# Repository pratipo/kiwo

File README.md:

# kiwo
post digital knitting, hybrid fabrication, digital crafts, social looming
 
> “El acto de tejer se convierte en una metáfora de la vida diaria, y también en una herramienta para construir espacio, construir grupos y comunidades, actividades e ideales que de otra forma permanecerían escondidos, olvidados o perdidos” 
> In The Loop, Knitting now. Jessica Hemmings (2010)

###Overview
Kiwo is an augmented rag loom, an artifact for hybrid fabric manufacture. It's a digital, interactive loom that can manage complex patterns in a user-friendly way. 

An augmented loom is not an elektroknit machine (a fully automated robot into which you feed a pattern and it takes over both the act of producing and the product), nor a traditional loom that gives no feedback to the user. Kiwo is a prototype designed to preserve all the properties of the craft production activity (inherent to the product and the social, physical and emotional activity itself) while speeding up the ability to learn new stitches and transform the number of patterns created or shared into tangible fabrics.

Using a series of simple sensors and actuators Kiwo is able to read the user's work and guide how fabrics are made out of different stitches. Multi-coloured patterns can be made too, by using several strands of colour to produce pictures, motifs and symbols. These complex patterns can be computer generated and easily transferred to the artefact (previously or) after they have been (self)made or distributed.  

A mobile app allows users to transfer these patterns into Kiwo, while enjoying outdoor and social life.

###Tech

A MEAN2 stack ecosystem plus an electronic device thaqt receives knitting-pattern data through BLE
 * Mongo schema wip
 * Ionic2 port wip
 * Nodejs wip
 
 * Pcb and bom wip (ws2812 + ble + 328)
 * Loom body and needle wip
 * Stitch detection wip

second poc. needle A vs needle B

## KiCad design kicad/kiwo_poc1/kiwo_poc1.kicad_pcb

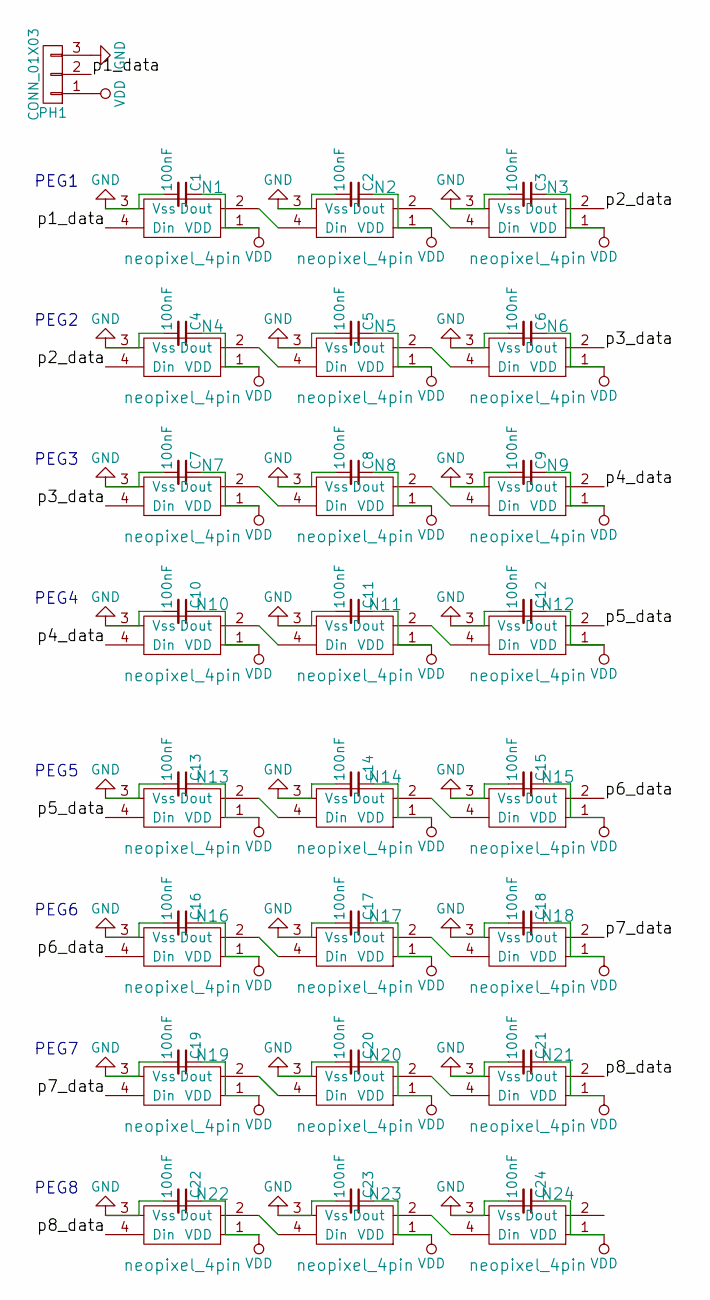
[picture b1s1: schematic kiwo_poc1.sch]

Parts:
C1, C2, C3, C4, C5, C6, C7, C8, C9, C10, C11, C12, C13, C15, C16, C17, C18, C19, C20, C21, C22, C23, C24: 100nF; C_0603
N1, N2, N3, N4, N5, N6, N7, N8, N9, N10, N11, N12, N13, N14, N15, N16, N17, N18, N19, N20, N21, N22, N23, N24: neopixel_4pin; neopixel_4pins
PH1: CONN_01X03; Pin_Header_Angled_1x03
c14: 100nF; C_0603

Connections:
/p1_data: N1.4 (Din), PH1.2
/p2_data: N3.2 (Dout), N4.4 (Din)
/p3_data: N6.2 (Dout), N7.4 (Din)
/p4_data: N9.2 (Dout), N10.4 (Din)
/p5_data: N12.2 (Dout), N13.4 (Din)
/p6_data: N15.2 (Dout), N16.4 (Din)
/p7_data: N18.2 (Dout), N19.4 (Din)
/p8_data: N21.2 (Dout), N22.4 (Din)
GND: C1.2, C2.2, C3.2, C4.2, C5.2, C6.2, C7.2, C8.2, C9.2, C10.2, C11.2, C12.2, C13.2, C15.2, C16.2, C17.2, C18.2, C19.2, C20.2, C21.2, C22.2, C23.2, C24.2, N1.3 (Vss), N2.3 (Vss), N3.3 (Vss), N4.3 (Vss), N5.3 (Vss), N6.3 (Vss), N7.3 (Vss), N8.3 (Vss), N9.3 (Vss), N10.3 (Vss), N11.3 (Vss), N12.3 (Vss), N13.3 (Vss), N14.3 (Vss), N15.3 (Vss), N16.3 (Vss), N17.3 (Vss), N18.3 (Vss), N19.3 (Vss), N20.3 (Vss), N21.3 (Vss), N22.3 (Vss), N23.3 (Vss), N24.3 (Vss), PH1.3, c14.2
unnamed: N1.2 (Dout), N2.4 (Din)
unnamed: N2.2 (Dout), N3.4 (Din)
unnamed: N4.2 (Dout), N5.4 (Din)
unnamed: N5.2 (Dout), N6.4 (Din)
unnamed: N7.2 (Dout), N8.4 (Din)
unnamed: N8.2 (Dout), N9.4 (Din)
unnamed: N10.2 (Dout), N11.4 (Din)
unnamed: N11.2 (Dout), N12.4 (Din)
unnamed: N13.2 (Dout), N14.4 (Din)
unnamed: N14.2 (Dout), N15.4 (Din)
unnamed: N16.2 (Dout), N17.4 (Din)
unnamed: N17.2 (Dout), N18.4 (Din)
unnamed: N19.2 (Dout), N20.4 (Din)
unnamed: N20.2 (Dout), N21.4 (Din)
unnamed: N22.2 (Dout), N23.4 (Din)
unnamed: N23.2 (Dout), N24.4 (Din)
VDD: C1.1, C2.1, C3.1, C4.1, C5.1, C6.1, C7.1, C8.1, C9.1, C10.1, C11.1, C12.1, C13.1, C15.1, C16.1, C17.1, C18.1, C19.1, C20.1, C21.1, C22.1, C23.1, C24.1, N1.1 (VDD), N2.1 (VDD), N3.1 (VDD), N4.1 (VDD), N5.1 (VDD), N6.1 (VDD), N7.1 (VDD), N8.1 (VDD), N9.1 (VDD), N10.1 (VDD), N11.1 (VDD), N12.1 (VDD), N13.1 (VDD), N14.1 (VDD), N15.1 (VDD), N16.1 (VDD), N17.1 (VDD), N18.1 (VDD), N19.1 (VDD), N20.1 (VDD), N21.1 (VDD), N22.1 (VDD), N23.1 (VDD), N24.1 (VDD), PH1.1, c14.1

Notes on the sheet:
PEG1
PEG2
PEG3
PEG4
PEG5
PEG6
PEG7
PEG8

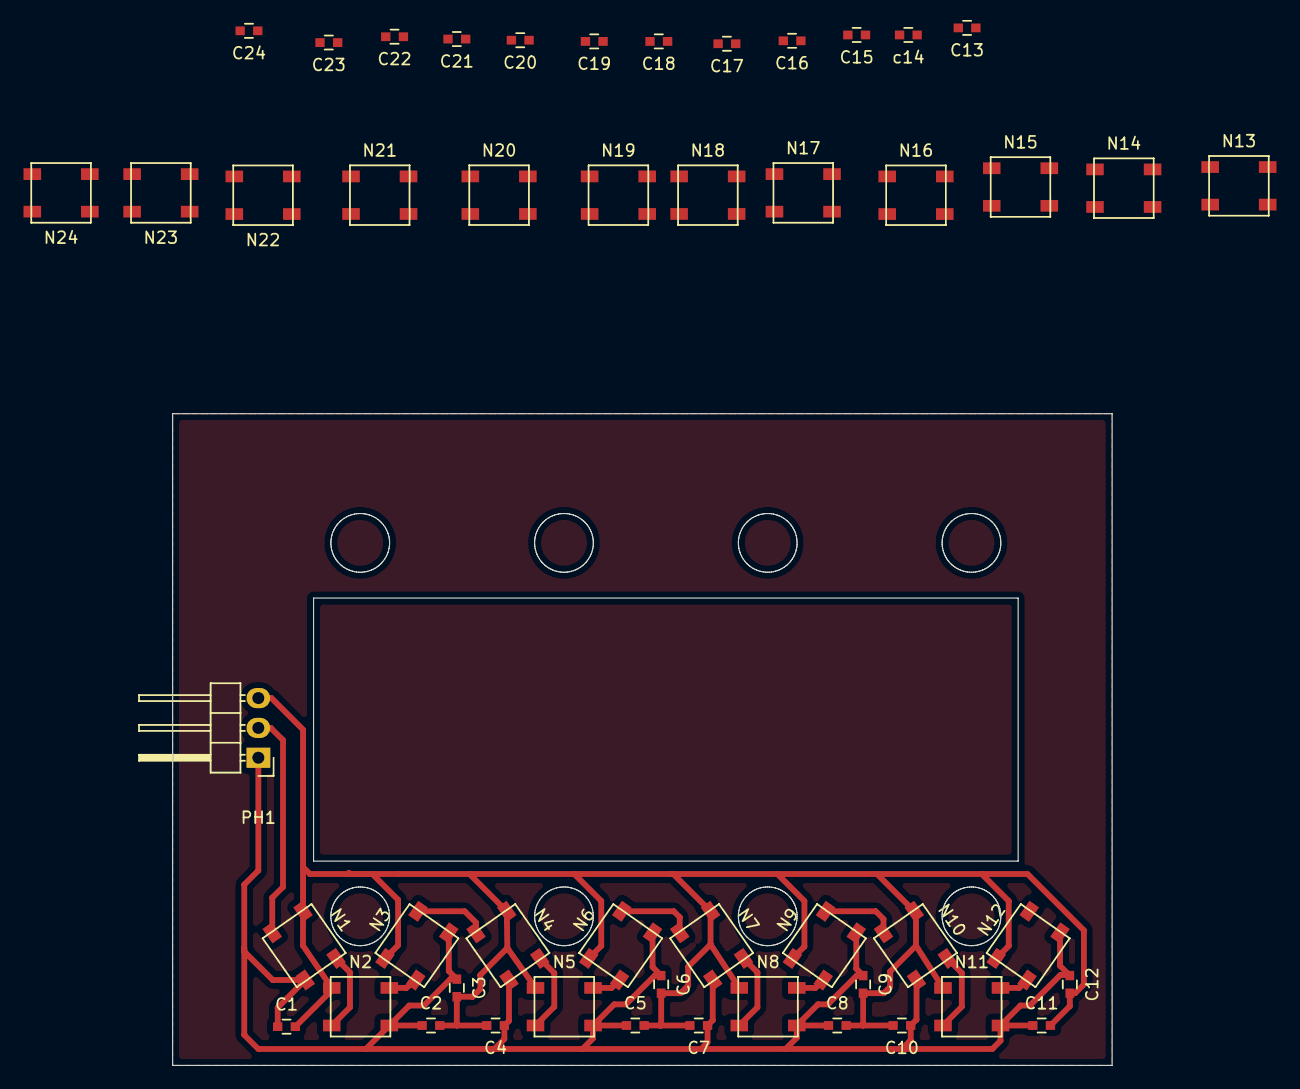
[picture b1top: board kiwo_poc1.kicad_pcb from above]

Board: 2 copper layers, 80.0 x 55.5 mm, 49 parts (0 on the bottom side), 26 nets.

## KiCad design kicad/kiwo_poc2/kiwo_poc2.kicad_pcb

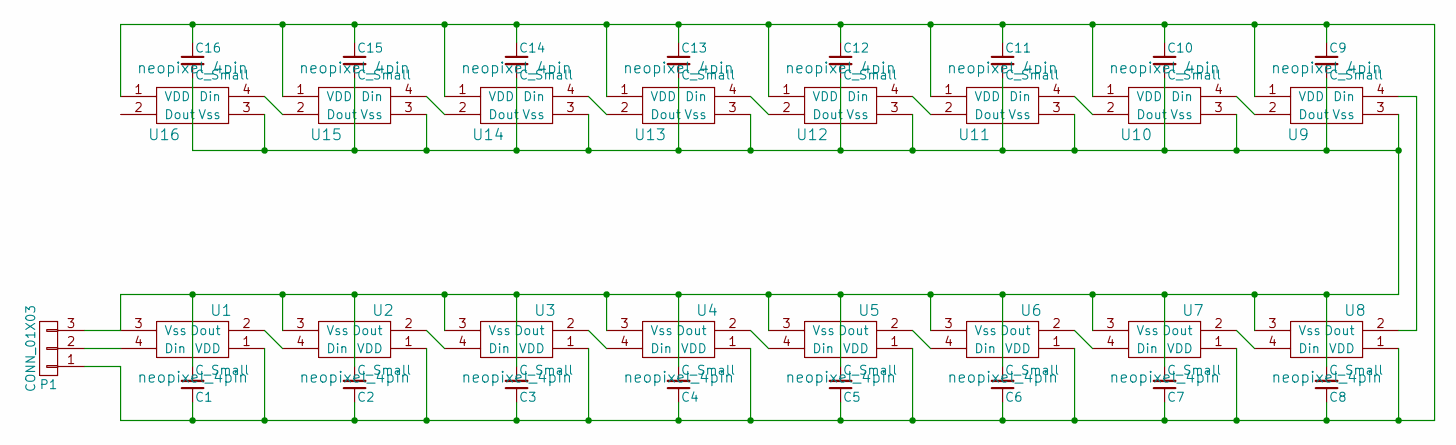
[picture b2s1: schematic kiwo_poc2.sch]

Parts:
C1, C2, C3, C4, C5, C6, C7, C8, C9, C10, C11, C12, C13, C14, C15, C16: C_Small; C_0603_HandSoldering
P1: CONN_01X03; Pin_Header_Angled_1x03
U1, U2, U3, U4, U5, U6, U7, U8, U9, U10, U11, U12, U13, U14, U15, U16: neopixel_4pin; neopixel_4pins

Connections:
unnamed: C1.1, C2.1, C3.1, C4.1, C5.1, C6.1, C7.1, C8.1, C9.1, C10.1, C11.1, C12.1, C13.1, C14.1, C15.1, C16.1, P1.1, U1.1 (VDD), U2.1 (VDD), U3.1 (VDD), U4.1 (VDD), U5.1 (VDD), U6.1 (VDD), U7.1 (VDD), U8.1 (VDD), U9.1 (VDD), U10.1 (VDD), U11.1 (VDD), U12.1 (VDD), U13.1 (VDD), U14.1 (VDD), U15.1 (VDD), U16.1 (VDD)
unnamed: C1.2, C2.2, C3.2, C4.2, C5.2, C6.2, C7.2, C8.2, C9.2, C10.2, C11.2, C12.2, C13.2, C14.2, C15.2, C16.2, P1.3, U1.3 (Vss), U2.3 (Vss), U3.3 (Vss), U4.3 (Vss), U5.3 (Vss), U6.3 (Vss), U7.3 (Vss), U8.3 (Vss), U9.3 (Vss), U10.3 (Vss), U11.3 (Vss), U12.3 (Vss), U13.3 (Vss), U14.3 (Vss), U15.3 (Vss), U16.3 (Vss)
unnamed: P1.2, U1.4 (Din)
unnamed: U1.2 (Dout), U2.4 (Din)
unnamed: U2.2 (Dout), U3.4 (Din)
unnamed: U3.2 (Dout), U4.4 (Din)
unnamed: U4.2 (Dout), U5.4 (Din)
unnamed: U5.2 (Dout), U6.4 (Din)
unnamed: U6.2 (Dout), U7.4 (Din)
unnamed: U7.2 (Dout), U8.4 (Din)
unnamed: U8.2 (Dout), U9.4 (Din)
unnamed: U10.2 (Dout), U11.4 (Din)
unnamed: U9.2 (Dout), U10.4 (Din)
unnamed: U11.2 (Dout), U12.4 (Din)
unnamed: U12.2 (Dout), U13.4 (Din)
unnamed: U13.2 (Dout), U14.4 (Din)
unnamed: U14.2 (Dout), U15.4 (Din)
unnamed: U15.2 (Dout), U16.4 (Din)

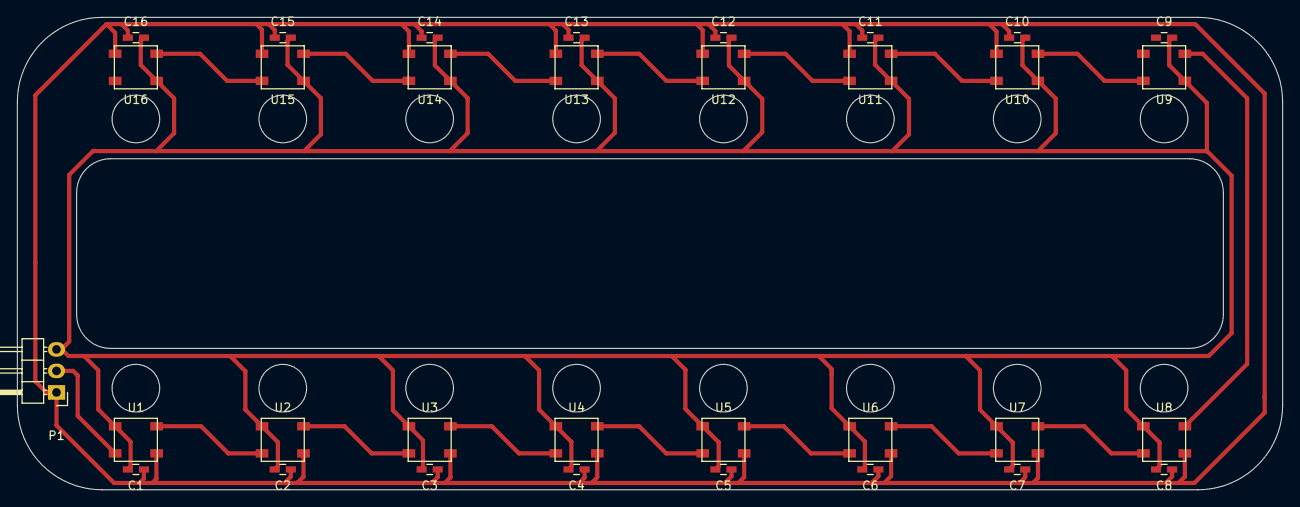
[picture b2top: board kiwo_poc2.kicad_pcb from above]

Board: 2 copper layers, 149.4 x 55.8 mm, 33 parts (0 on the bottom side), 18 nets.

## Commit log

2016-09-09 end of the MLP residency
2016-09-09 wip proof of concept2... migrating to ionic 2
